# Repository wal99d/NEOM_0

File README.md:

NEOM_IoT
=======
This repo contains all design file for NOEM_IoT v0 Rev2.0 hardware along with its firmware. 

It's built with simplicity in mind using new STM32F401CEU6 MCU which have below 
> ***features:***
> - Core is ARM 32-bit Cortex-M4 with FPU.
> - Power required between 1.7v to 3.6V.
> - Up to 4 SPI
> - Up to 3 I2C
> - Up to 3 USART
> - 12 bits ADC up to 16 channels.
> - Up to 11 Timers
> - 512KB Flash and 96Kbyte SRAM which is very useful for specialized IoT applications.
> - USB 2.0 Full Speed Support.
> - Debug mode in Serial wire debug (SWD).

***TODO:***

: Firmware

***Author:***
[@wal99d](https://twitter.com/wal99d)

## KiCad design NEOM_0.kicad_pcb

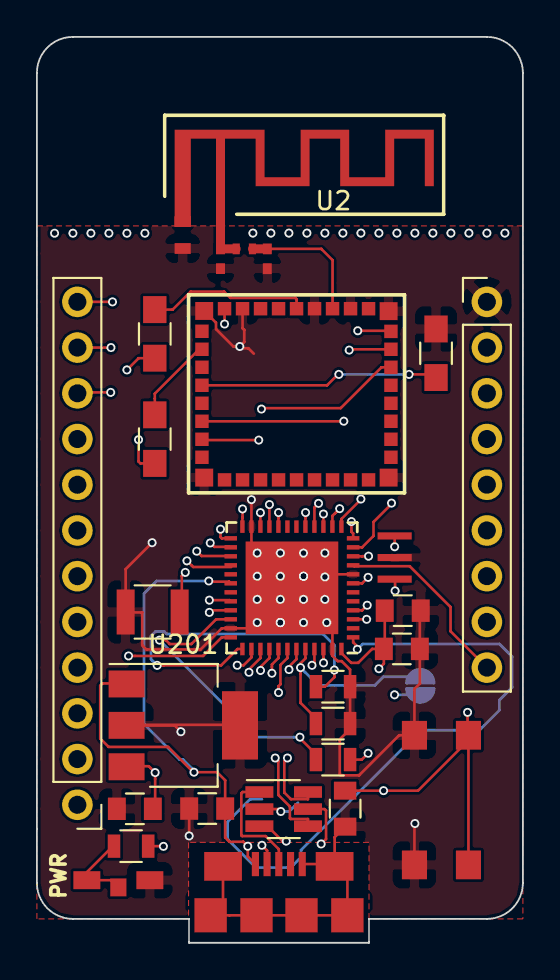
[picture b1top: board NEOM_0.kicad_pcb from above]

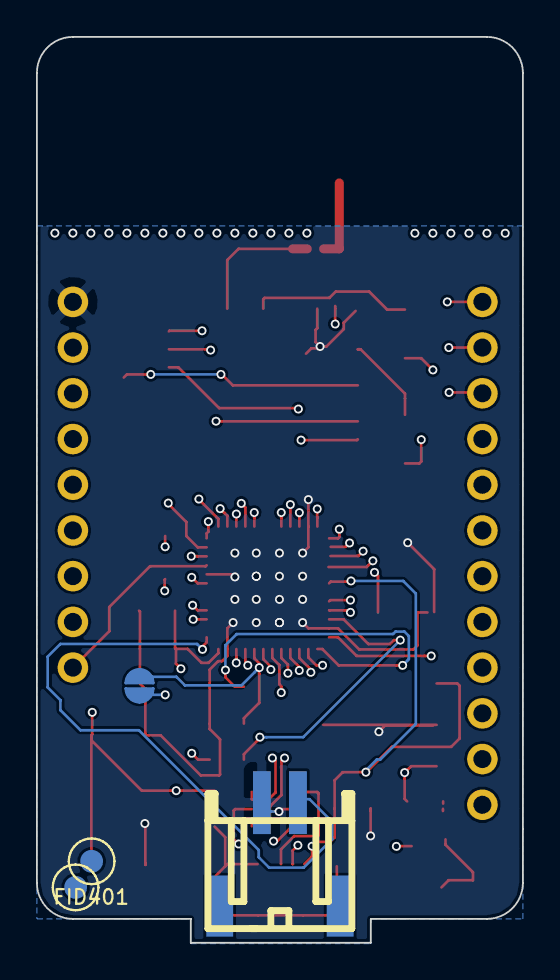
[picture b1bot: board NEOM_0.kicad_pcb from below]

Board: 4 copper layers, 27.0 x 50.3 mm, 31 parts (4 on the bottom side), 44 nets.

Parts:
C1, C2: NF; C_0402_NoSilk
C201: 0.47u; C_0805
C202: 33u; C_0805
C203: 0.1u; C_0805
C204: 10n; C_0805
C205: 1u; C_0805
C401: C; C_1210
D201: LED; 0805_LED
FID401, FID402: FIDUCIAL; MF_Aesthetics-FIDUCIAL_100MIL
JP401: Jumper_NO_Small; JUMPER-SOLDER-SMD
P1: CONN_01X09; Pin_Header_Straight_1x09_Pitch2.54mm
P402: CONN_01X02; s2b-ph-sm4-tb
P403: CONN_01X12; Pin_Header_Straight_1x12_Pitch2.54mm
R1, R3: 100k; R_0805_HandSoldering
R2: 1k; R_0805_HandSoldering
R4: 0; R_0402_NoSilk
R201, R401: 680; R_0805
R402, R403: 100K; R_0805
SW201: SPST; SW_SPST
U1: AMW007R
U2: 2.4Ghz_Ant1; 2.4Ghz_PCB_Antenna1
U3: USBLC6-2; SOT-23-6_Handsoldering
U201: LM3940; SOT-223
U302: USB_Micro_B; MICRO_USB_B_Type
U401: 16Mhz
U402: STM32F401CEU6; QFN-48-1EP_7x7mm_Pitch0.5mm

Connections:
+3V3: C202.2, C204.1, C205.1, JP401.2, P1.9, R3.2, R201.1, R403.1, U1.38, U201.3, U402.9, U402.24, U402.36, U402.48
/Power_Managment/NRST: C203.1, P403.1, SW201.2, U402.7
/Power_Managment/VBUS: C201.2, U3.5, U201.1, U302.1, U402.30
/STM32F401CEU6/BOOT0: JP401.1, R401.1, U402.44
/STM32F401CEU6/PA4: P1.8, U402.14
/STM32F401CEU6/PA5: P1.7, U402.15
/STM32F401CEU6/PA6: P1.6, U402.16
/STM32F401CEU6/PA7: P1.5, U402.17
/STM32F401CEU6/PA15: P403.9, U402.38
/STM32F401CEU6/PB2: P1.4, U402.20
/STM32F401CEU6/PB3: P403.8, U402.39
/STM32F401CEU6/PB4: P403.7, U402.40
/STM32F401CEU6/PB5: P403.6, U402.41
/STM32F401CEU6/PB6: P403.5, U402.42
/STM32F401CEU6/PB7: P403.4, U402.43
/STM32F401CEU6/PB8: P403.3, U402.45
/STM32F401CEU6/PB9: P403.2, U402.46
/STM32F401CEU6/PB10: P1.3, U402.21
/STM32F401CEU6/PB12: P1.2, U402.25
/STM32F401CEU6/PB13: P403.12, U402.26
/STM32F401CEU6/PB14: P403.11, U402.27
/STM32F401CEU6/PB15: P403.10, U402.28
/STM32F401CEU6/SWCLK: R402.1, U402.37
/STM32F401CEU6/SWDIO: R403.2, U402.34
/STM32F401CEU6/UART_CTS: U1.27, U402.10
/STM32F401CEU6/UART_RTS: U1.28, U402.11
/STM32F401CEU6/UART_RX: U1.7, U402.12
/STM32F401CEU6/UART_TX: U1.8, U402.13
/STM32F401CEU6/USB+: U3.6, U402.33
/STM32F401CEU6/USB-: U3.4, U402.32
GND: C1.2, C2.2, C201.1, C202.1, C203.2, C204.2, C205.2, C401.2, D201.1, P1.1, P402.1, R1.2, R401.2, R402.2, SW201.1, U1.1, U1.10, U1.20, U1.29, U1.31, U1.33, U1.37, U2.2, U3.2, U201.2, U201.4, U302.0, U302.5, U401.2, U402.8, U402.23, U402.35, U402.47, U402.49
unnamed: C1.1, R4.2, U1.32
unnamed: C2.1, R4.1, U2.1
unnamed: C401.1, U402.22
unnamed: D201.2, R201.2
unnamed: P402.2, U402.1
unnamed: R1.1, U1.5
unnamed: R2.1, U1.3
unnamed: R2.2, U1.26
unnamed: R3.1, U1.34
unnamed: U3.1, U302.3
unnamed: U3.3, U302.2
unnamed: U401.1, U402.4
unnamed: U401.3, U402.3

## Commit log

2017-11-19 First Commit..
2017-11-20 Updated the PCB unconnected GND pad..
2017-11-20 Updated README.md..
2017-11-21 Added BAT pin for external battery board..
2017-11-23 Updated PCB with logo..
2017-11-24 Updated PCB with deminsion and Fab layer..
2017-11-24 Updated PCB with Footprint Fab..
2017-11-25 Updated PCB: added defferintial pair routing to USB+/-...
2017-11-25 Added Board Mechnical Dimensions...
2017-12-13 Added modified files..
2017-12-13 Removed NEOM_0.zip
2017-12-13 Removed non needed files...
2017-12-25 Updated to Rev2.0
2017-12-26 Updated..
2017-12-26 Updated...

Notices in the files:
NEOM_0.kicad_pcb:
CERN OHL version 1.2.
